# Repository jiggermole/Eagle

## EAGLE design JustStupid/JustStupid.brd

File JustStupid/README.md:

This is just stupid.  Have a 300W led cob.  103VDC forward voltage 4.5A ish driving current.
I needed a stupidly simple power supply to see how bright a 36k lumen light is.
takes wall power, rectifies it and uses a very small ldo regulator for gate power for the 
fat mosfets.  Power resistors to limit current through COB.

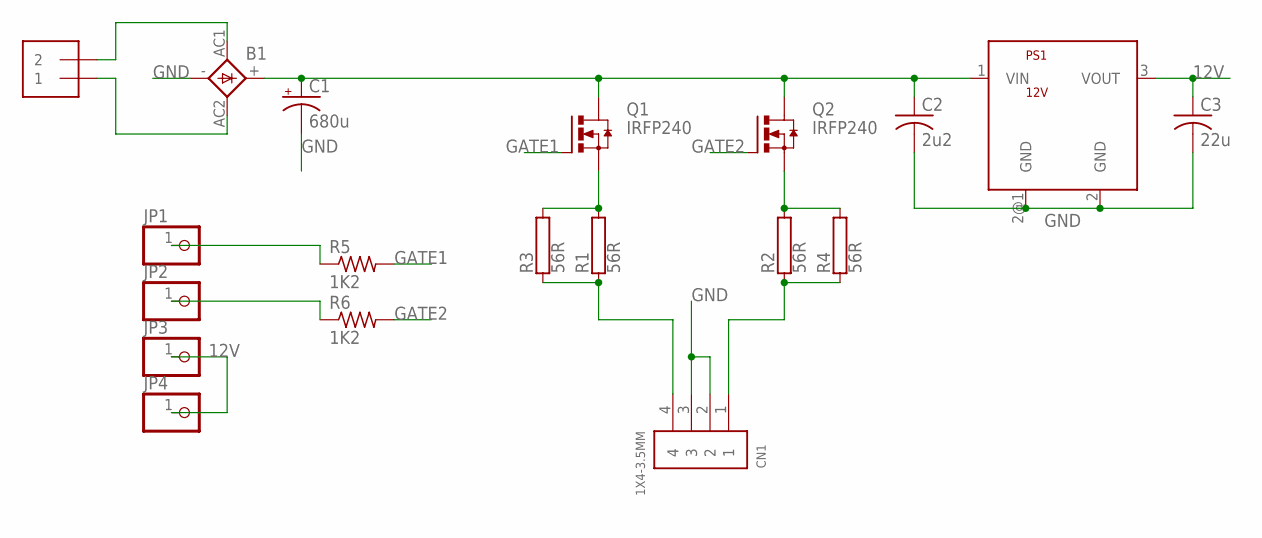
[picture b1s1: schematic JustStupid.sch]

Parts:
ACIN: 1X2-3.5MM
B1: KBU
C1: 680u; PCPIN_CAP
C2: 2u2; C2220K
C3: 22u; C1206
CN1: 1X4-3.5MM; 1X04-3.5MM
JP1, JP2, JP3, JP4: PINHD-1X1; 1X01
PS1: 12V; SOT89
Q1, Q2: IRFP240; TO247BV
R1, R2, R3, R4: 56R; TO-247-2V
R5, R6: 1K2; R1206

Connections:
12V: C3.1, JP3.1, JP4.1, PS1.3 (VOUT)
GATE1: Q1.G, R5.2
GATE2: Q2.G, R6.2
GND: B1.-, C1.P$1 (-), C2.2, C3.2, CN1.2, CN1.3, PS1.2 (GND), PS1.2@1 (GND)
unnamed: ACIN.1, B1.AC2
unnamed: ACIN.2, B1.AC1
unnamed: B1.+, C1.P$2 (+), C2.1, PS1.1 (VIN), Q1.D, Q2.D
unnamed: JP1.1, R5.1
unnamed: CN1.4, R1.1, R3.1
unnamed: CN1.1, R2.1, R4.1
unnamed: Q1.S, R1.2, R3.2
unnamed: Q2.S, R2.2, R4.2
unnamed: JP2.1, R6.1

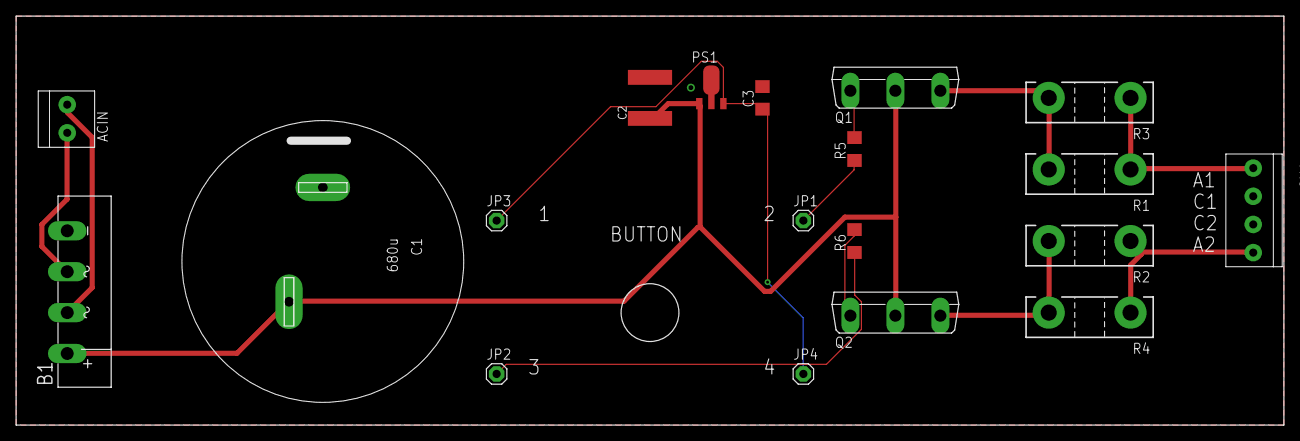
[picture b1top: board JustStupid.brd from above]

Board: 2 copper layers, 157.5 x 50.8 mm, 19 parts (0 on the bottom side), 13 nets.

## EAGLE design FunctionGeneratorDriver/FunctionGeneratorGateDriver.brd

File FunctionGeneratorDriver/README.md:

we have a function generator and a decent bench power supply.
This board is to allow the function generator to drive bigger loads.
Board made through oshpark.  
Uses turret pins for alagator clips and some jumpers so you can configure
low side or high side switching.
MCP14A0152 for the gate driver.
Si235DS for the n channel mosfet to do the driving.

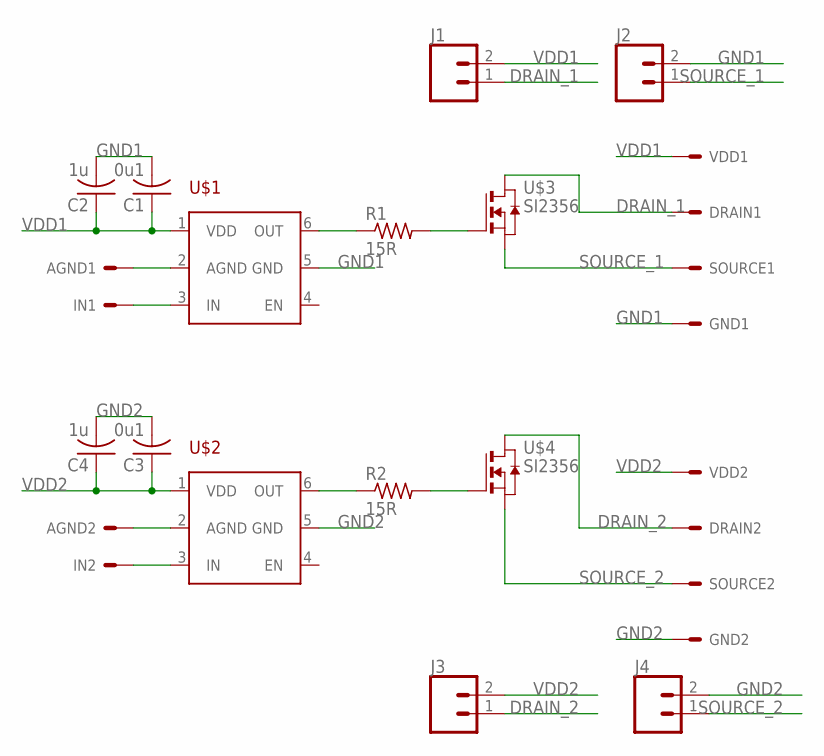
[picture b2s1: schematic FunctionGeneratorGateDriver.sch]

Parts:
AGND1, AGND2: P1X1; 1X01
C1, C3: 0u1; C1206
C2, C4: 1u; C1206
DRAIN1, DRAIN2: P1X1; 1X01
GND1, GND2: P1X1; 1X01
IN1, IN2: P1X1; 1X01
J1, J2, J3, J4: CONN_02; 1X02
R1, R2: 15R; R1206
SOURCE1, SOURCE2: P1X1; 1X01
U$1, U$2: MCP14A0152; SOT95P270X150-6
U$3, U$4: SI2356; SOT95P237X120-3
VDD1, VDD2: P1X1; 1X01

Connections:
DRAIN_1: DRAIN1.1, J1.1, U$3.3 (D)
DRAIN_2: DRAIN2.1, J3.1, U$4.3 (D)
GND1: C1.2, C2.2, GND1.1, J2.2, U$1.5 (GND)
GND2: C3.2, C4.2, GND2.1, J4.2, U$2.5 (GND)
unnamed: R2.1, U$2.6 (OUT)
unnamed: R2.2, U$4.1 (G)
unnamed: R1.1, U$1.6 (OUT)
unnamed: R1.2, U$3.1 (G)
unnamed: AGND1.1, U$1.2 (AGND)
unnamed: IN1.1, U$1.3 (IN)
unnamed: AGND2.1, U$2.2 (AGND)
unnamed: IN2.1, U$2.3 (IN)
SOURCE_1: J2.1, SOURCE1.1, U$3.2 (S)
SOURCE_2: J4.1, SOURCE2.1, U$4.2 (S)
VDD1: C1.1, C2.1, J1.2, U$1.1 (VDD), VDD1.1
VDD2: C3.1, C4.1, J3.2, U$2.1 (VDD), VDD2.1

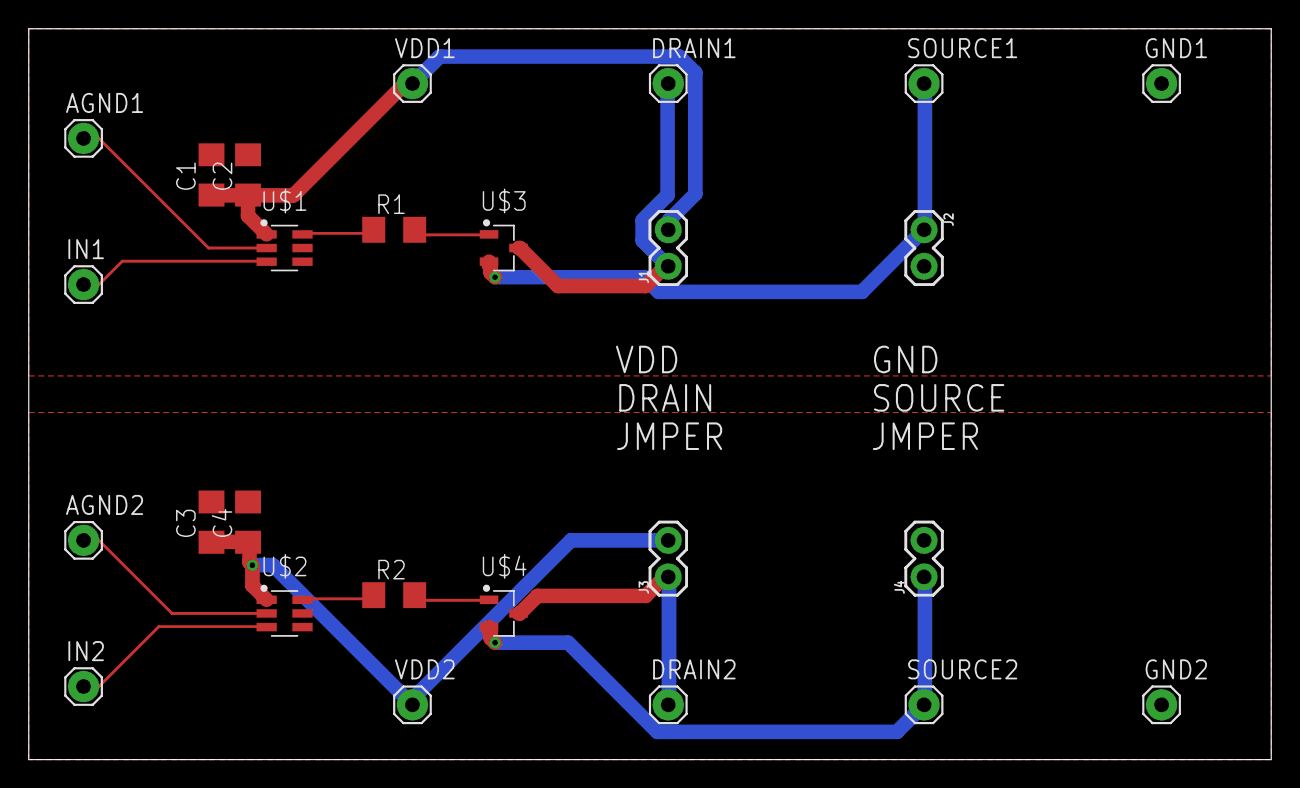
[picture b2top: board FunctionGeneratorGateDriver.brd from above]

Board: 2 copper layers, 86.4 x 50.8 mm, 26 parts (0 on the bottom side), 16 nets.

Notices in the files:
parts and their libraries:
SparkFun-Connectors: Licensing: Creative Commons ShareAlike 4.0 International - https://creativecommons.org/licenses/by-sa/4.0
